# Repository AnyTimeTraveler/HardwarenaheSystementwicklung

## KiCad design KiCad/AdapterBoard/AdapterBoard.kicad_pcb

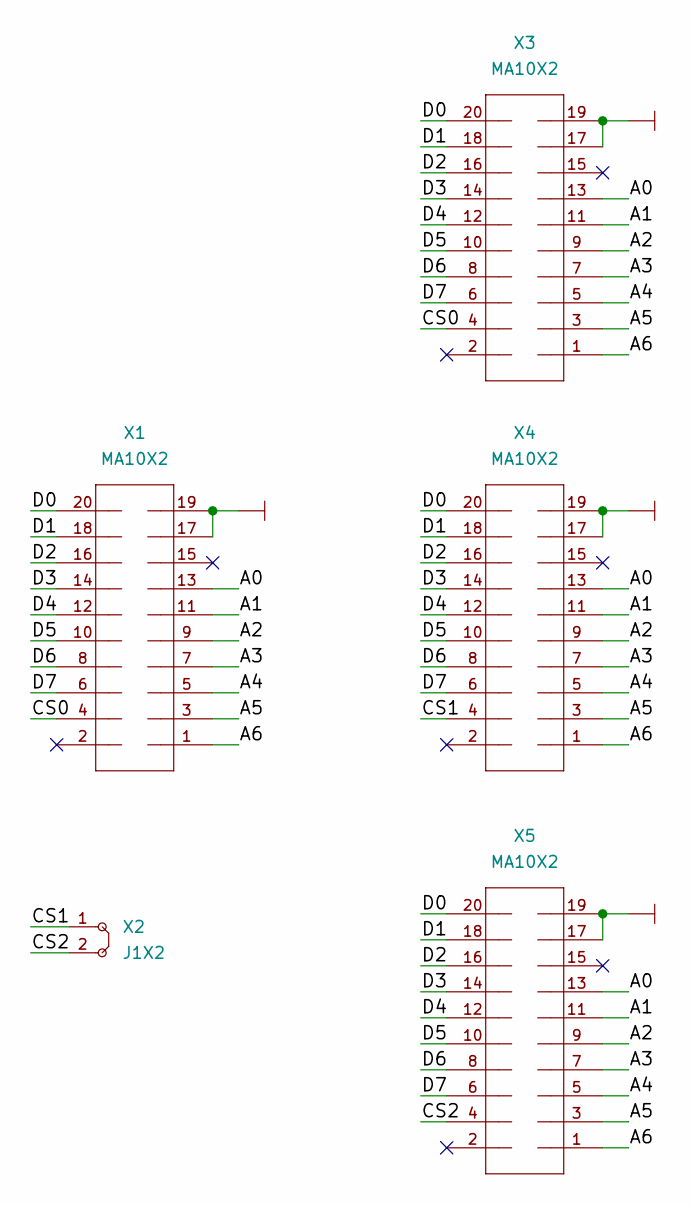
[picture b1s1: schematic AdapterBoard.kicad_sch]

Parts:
X1, X3, X4, X5: MA10X2; PinHeader_2x10_P2.54mm_Vertical
X2: J1X2; PinHeader_1x02_P2.54mm_Vertical

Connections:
/A0: X1.13, X3.13, X4.13, X5.13
/A1: X1.11, X3.11, X4.11, X5.11
/A2: X1.9, X3.9, X4.9, X5.9
/A3: X1.7, X3.7, X4.7, X5.7
/A4: X1.5, X3.5, X4.5, X5.5
/A5: X1.3, X3.3, X4.3, X5.3
/A6: X1.1, X3.1, X4.1, X5.1
/CS0: X1.4, X3.4
/CS1: X2.1, X4.4
/CS2: X2.2, X5.4
/D0: X1.20, X3.20, X4.20, X5.20
/D1: X1.18, X3.18, X4.18, X5.18
/D2: X1.16, X3.16, X4.16, X5.16
/D3: X1.14, X3.14, X4.14, X5.14
/D4: X1.12, X3.12, X4.12, X5.12
/D5: X1.10, X3.10, X4.10, X5.10
/D6: X1.8, X3.8, X4.8, X5.8
/D7: X1.6, X3.6, X4.6, X5.6
GND: X1.17, X1.19, X3.17, X3.19, X4.17, X4.19, X5.17, X5.19

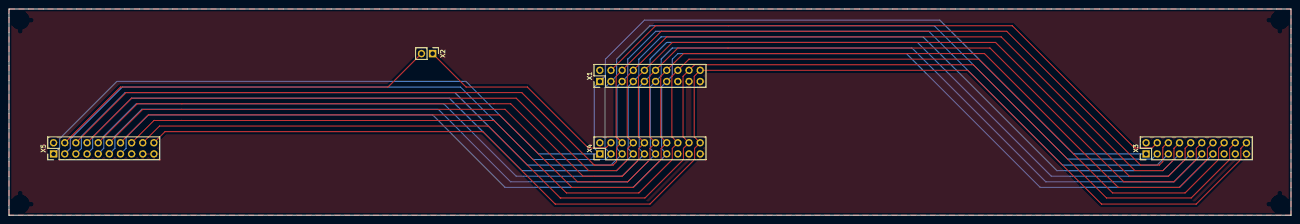
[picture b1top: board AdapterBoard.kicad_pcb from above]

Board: 2 copper layers, 292.1 x 47.0 mm, 5 parts (0 on the bottom side), 19 nets.

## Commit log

2022-11-07 Connect Input devices and clean up a bit, some ERC fixes aswell
2022-11-08 finish schema and start with board
2022-11-16 Further Board allign
2022-11-21 All connected, check schematics
2022-12-28 Screen driver working
2022-12-29 Using register banks for interrupts
2022-12-30 Proper import and export of values and functions
2022-12-31 More work on gameticks and adding pieces
2022-12-31 Fix teris piece encoding
2022-12-31 Fix the damn remove_piece function
2022-12-31 Test: Allocations
2023-01-02 TETRIS PLAYS ITSELF! I'M THE MASTER OF THE UNIVERSE IN 873 BYTES!
2023-01-02 Add full line clearing
2023-01-03 Fix Register Bank 0 Address
2023-01-03 Fix rows falling
2023-01-03 Fix short jump for free keil compiler
2023-01-03 Remove testing code for line clearing
2023-01-11 WIP: Keyboard input
2023-01-13 WIP: Detect baudrate
2023-01-17 Implement baudrate detection
2023-01-17 Add other code to gitignore
2023-01-18 Fix undefined constants
2023-01-18 Add Constant for Debug LED
2023-01-18 Hoefully completed baudrate detection
2023-01-18 Remove unnecessary timer deactivation
2023-01-18 Replace small hack with intended small hack
2023-01-18 Add COLOUR
2023-01-19 Playable in the emulator
2023-01-19 Fix baudrate_detect
2023-01-25 Failed: Add gamestate
2023-01-25 Ignore measurements
2023-01-26 WIP: Reorganizing
2023-01-29 WIP: Refactor
2023-01-29 Fix all the compile errors
2023-02-01 Logic is 2 byte based, screen 3 byte based
2023-02-01 3 Screens work
2023-02-01 WIP: Draw Logo
